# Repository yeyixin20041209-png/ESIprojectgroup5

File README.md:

# Assistive Grasping Glove — ESI Group 5

An engineering project exploring a motor-driven glove to assist grasping. The system uses flex sensors to detect finger bending and a force-sensitive resistor (FSR) to detect object contact.

This repository contains the control firmware, PCB design files, and 3D-printable components.

## How It Works

The controller follows a basic grasp-and-release sequence:

1. **Idle:** Wait for both flex sensors to detect finger bending.
2. **Closing:** Drive the stepper motor to assist grasping.
3. **Hold:** Stop closing when the FSR detects object contact.
4. **Opening:** Reverse the motor when the release button is pressed.
5. **Return to idle:** Wait for the next grasp.

The firmware also includes controls for flex-sensor calibration and motor homing. Their behaviour depends on the firmware version.

## Hardware

- Two flex sensors
- One force-sensitive resistor (FSR)
- Stepper motor with a DRV8825 driver
- Arduino-compatible controller
- Release, reset/home, and calibration buttons
- Custom PCB
- 3D-printed mechanical components

## Repository Contents

| File or folder | Description |
|---|---|
| [`code.c++`](code.c++) | Glove control firmware |
| [`pcb/`](pcb/) | KiCad schematic, PCB layout, and project configuration |
| [`3d-print/`](3d-print/) | Printable models and available mechanical design files |

### PCB Files

Open `project.kicad_pro` in KiCad to access the PCB project.

- `project.kicad_sch` — circuit schematic
- `project.kicad_pcb` — PCB layout and routing
- `project.kicad_pro` — project configuration

### 3D Printing Files

The `3d-print/` folder contains the mechanical files provided for the project. Check model dimensions, orientation, and fit before printing.

## Firmware Pin Assignments

| Component | Pin |
|---|---|
| Flex sensor 1 | A0 |
| Flex sensor 2 | A1 |
| FSR | A2 |
| Release button | D3 |
| Reset/home button | D4 |
| Flex calibration button | D5 |
| DRV8825 STEP | D8 |
| DRV8825 DIR | D9 |
| DRV8825 ENABLE | D10 |

## Getting Started

1. Download or clone this repository.
2. Open the PCB project in KiCad and review the wiring.
3. Create an Arduino sketch and copy the selected firmware into it.
4. Select the board and port that match the controller.
5. Check pin assignments, sensor readings, motor direction, and thresholds against the assembled hardware.
6. Upload the firmware and test calibration, grasping, holding, and release.

Sensor thresholds and motor settings depend on the physical assembly and should be checked whenever the hardware or firmware changes.

## Project Team

Developed by **ESI Group 5**.

Team members and their responsibilities can be listed here as the project documentation is completed.

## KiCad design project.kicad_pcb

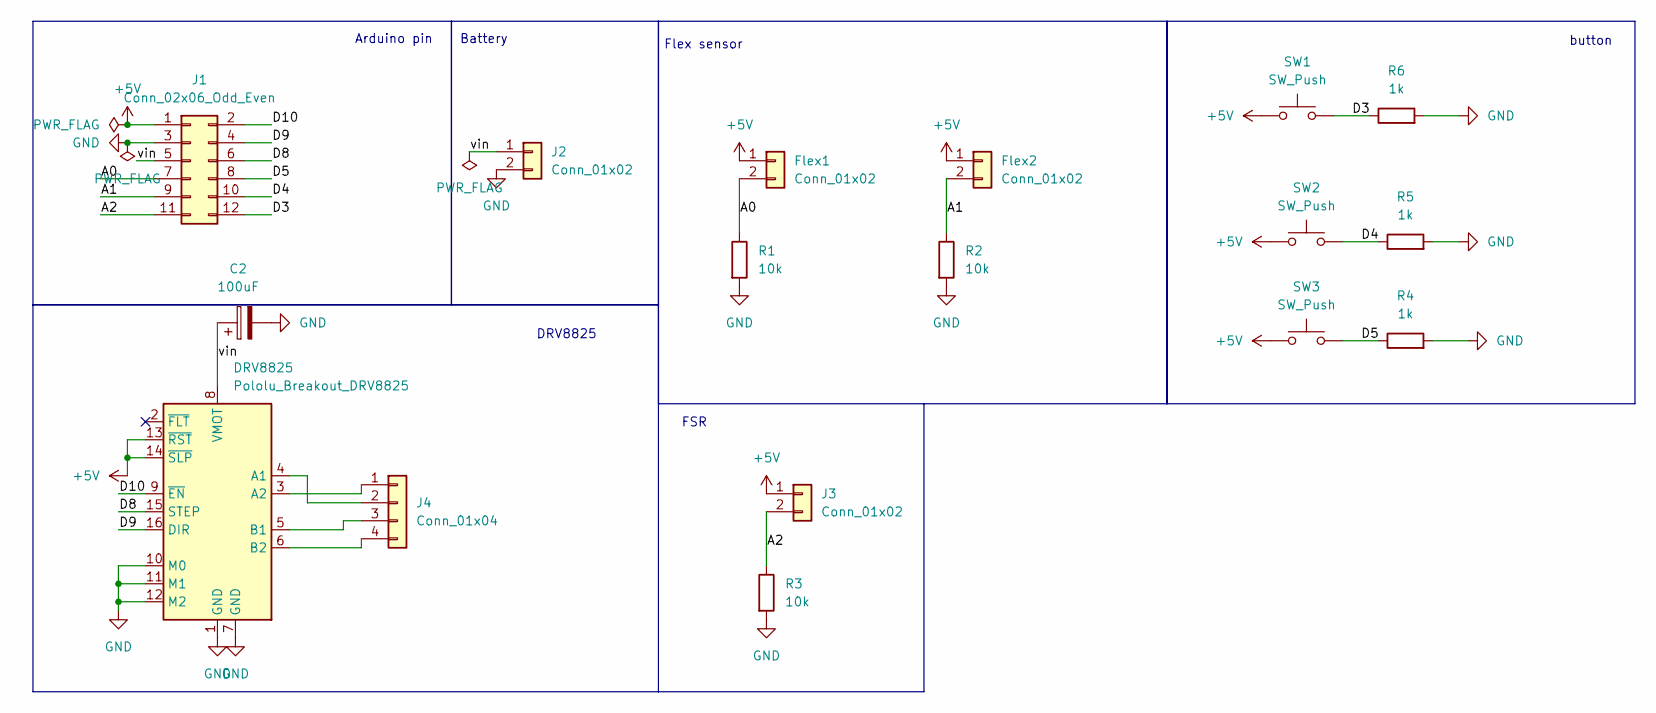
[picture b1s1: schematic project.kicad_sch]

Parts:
C2: 100uF; CP_Radial_D8.0mm_P3.50mm
DRV8825: Pololu_Breakout_DRV8825; Pololu_Breakout-16_15.2x20.3mm
Flex1, Flex2: Conn_01x02; PinHeader_1x02_P2.54mm_Vertical
J1: Conn_02x06_Odd_Even; PinHeader_2x06_P2.54mm_Vertical
J2, J3: Conn_01x02; PinHeader_1x02_P2.54mm_Vertical
J4: Conn_01x04; PinHeader_1x04_P2.54mm_Vertical
R1, R2, R3: 10k; R_Axial_DIN0207_L6.3mm_D2.5mm_P10.16mm_Horizontal
R4, R5, R6: 1k; R_Axial_DIN0207_L6.3mm_D2.5mm_P10.16mm_Horizontal
SW1, SW2, SW3: SW_Push; SW_PUSH_6mm

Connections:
+5V: DRV8825.13 (~RST), DRV8825.14 (~SLP), Flex1.1, Flex2.1, J1.1, J3.1, SW1.1, SW2.1, SW3.1
/A0: Flex1.2, J1.7, R1.1
/A1: Flex2.2, J1.9, R2.1
/A2: J1.11, J3.2, R3.1
/D3: J1.12, R6.1, SW1.2
/D4: J1.10, R5.1, SW2.2
/D5: J1.8, R4.1, SW3.2
/D8: DRV8825.15 (STEP), J1.6
/D9: DRV8825.16 (DIR), J1.4
/D10: DRV8825.9 (~EN), J1.2
/vin: C2.1, DRV8825.8 (VMOT), J1.5, J2.1
GND: C2.2, DRV8825.1 (GND), DRV8825.7 (GND), DRV8825.10 (M0), DRV8825.11 (M1), DRV8825.12 (M2), J1.3, J2.2, R1.2, R2.2, R3.2, R4.2, R5.2, R6.2
unnamed: DRV8825.4 (A1), J4.2
unnamed: DRV8825.3 (A2), J4.1
unnamed: DRV8825.5 (B1), J4.3
unnamed: DRV8825.6 (B2), J4.4

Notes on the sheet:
Arduino pin
Battery
Flex sensor
DRV8825
FSR
button

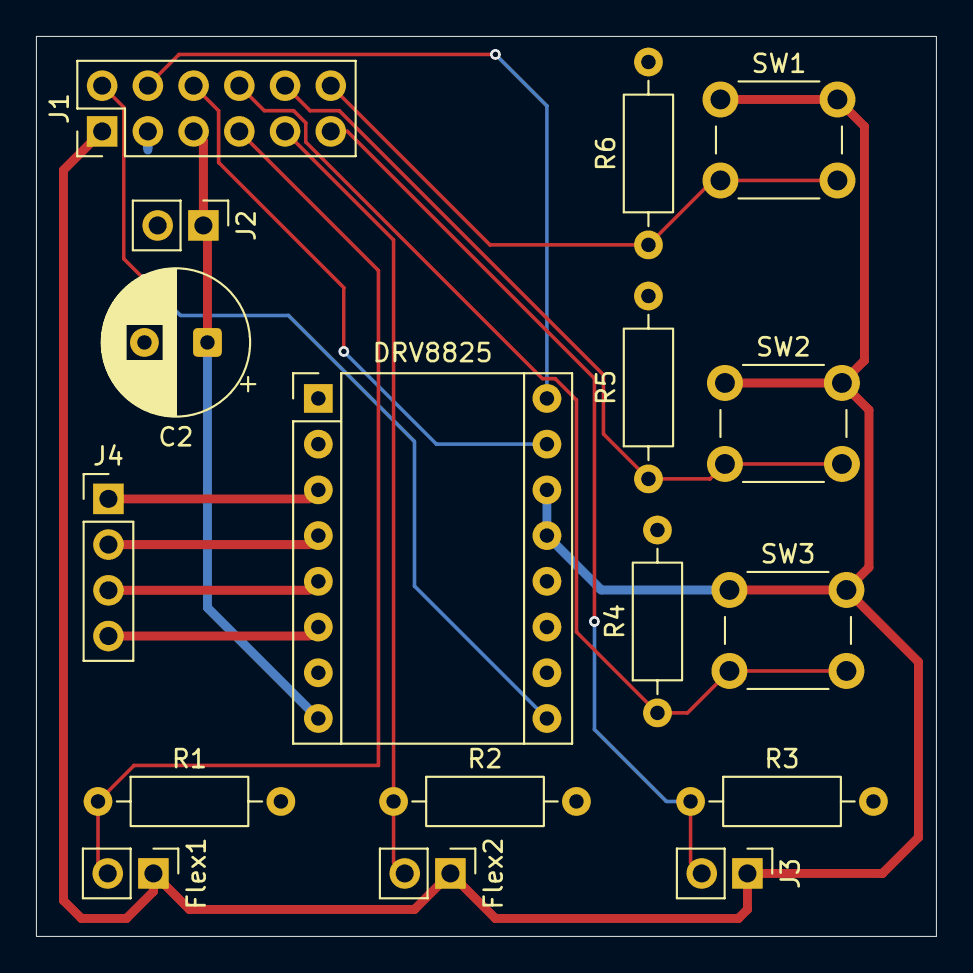
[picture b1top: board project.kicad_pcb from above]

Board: 2 copper layers, 50.0 x 50.0 mm, 17 parts (0 on the bottom side), 16 nets.
